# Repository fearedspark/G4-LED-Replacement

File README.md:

# G4 LED Replacement

This project is a high power LED replacement for 12V AC G4 halogen light bulbs.  
The main part of this project is the LED, a CMU1006-000-000N0Z0A30H.

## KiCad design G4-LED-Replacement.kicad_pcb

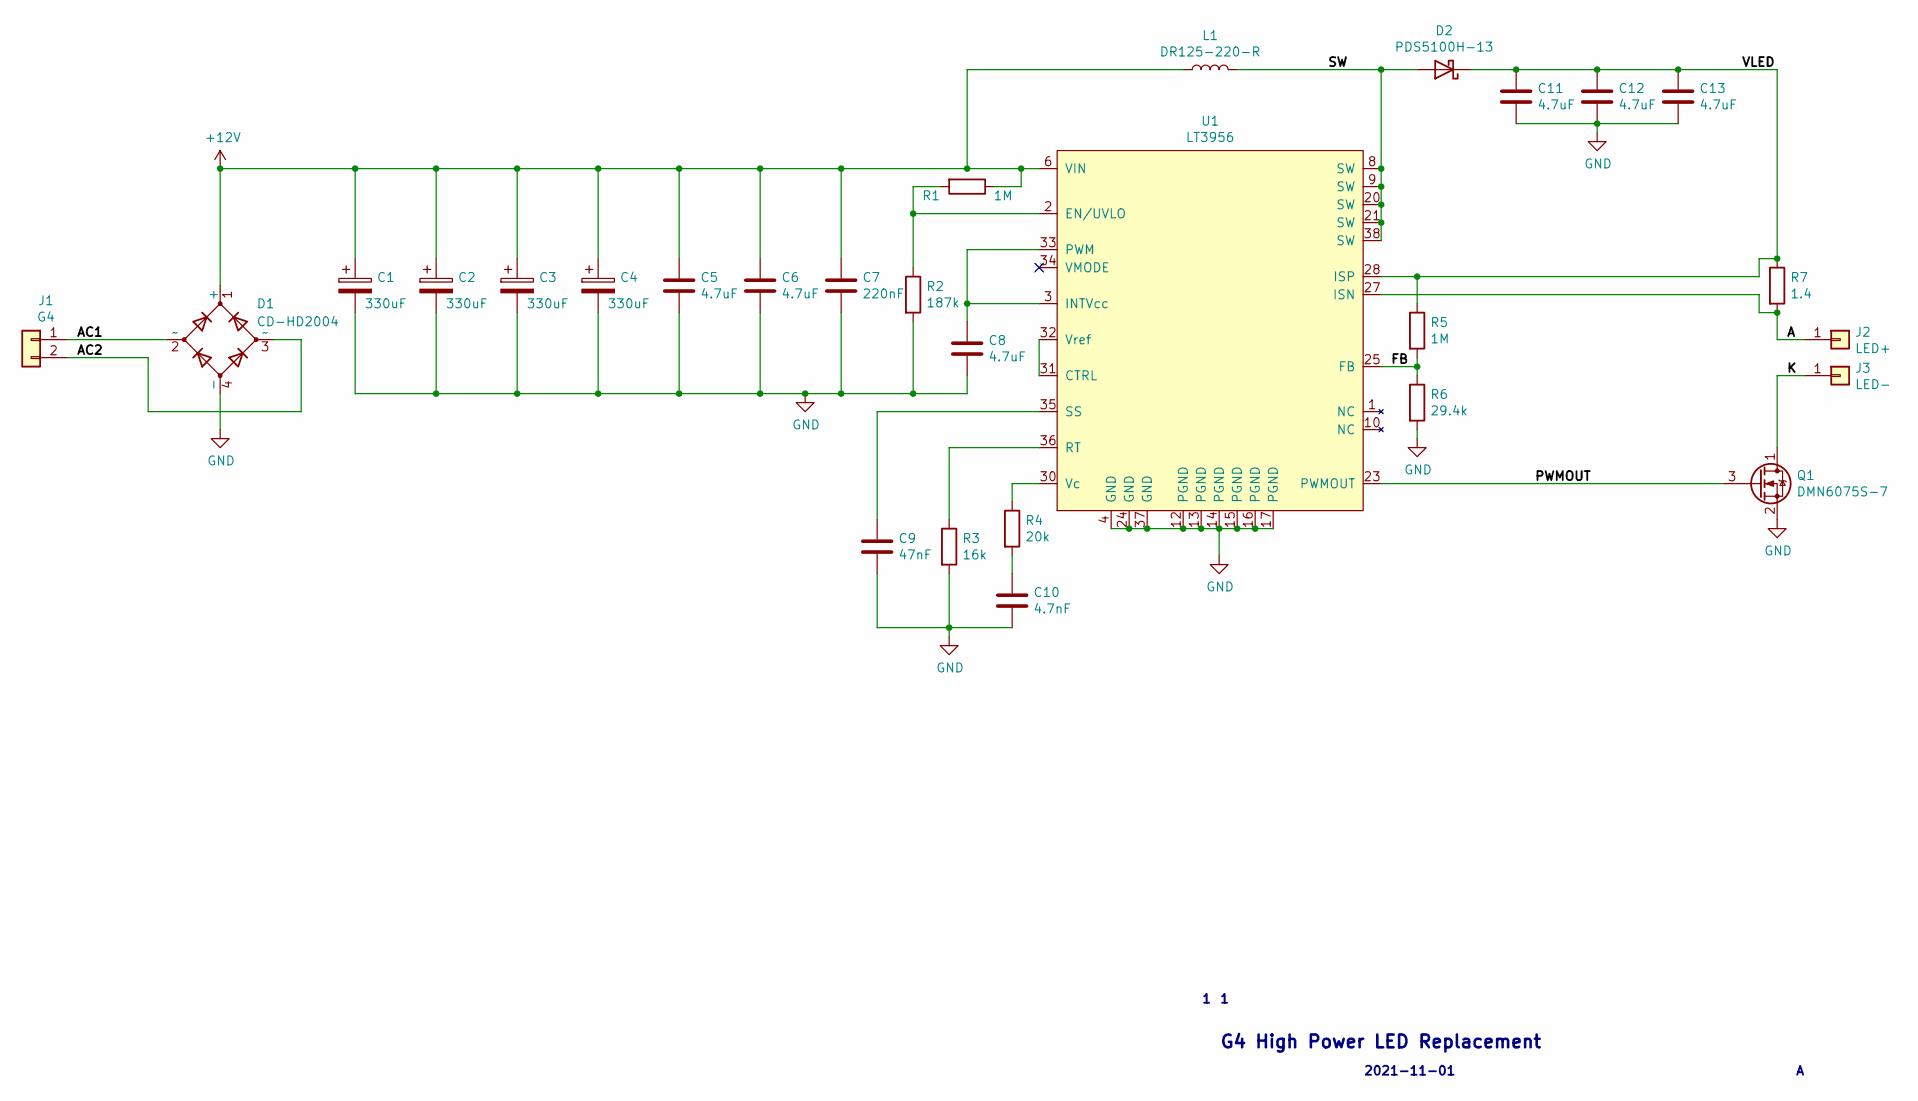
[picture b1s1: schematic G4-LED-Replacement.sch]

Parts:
C1, C2, C3, C4: 330uF; CP_EIA-7361-38_AVX-V
C5, C6, C8: 4.7uF; C_0805_2012Metric
C7: 220nF; C_0402_1005Metric
C9: 47nF; C_0402_1005Metric
C10: 4.7nF; C_0402_1005Metric
C11, C12, C13: 4.7uF; C_1206_3216Metric
D1: CD-HD2004; CD-HD2x(L)
D2: PDS5100H-13; D_PowerDI-5
J1: G4; G4_Pins
J2: LED+; TestPoint_Pad_D4.0mm
J3: LED-; TestPoint_Pad_D4.0mm
L1: DR125-220-R; L_12x12mm_H6mm
Q1: DMN6075S-7; SOT-23
R1, R5: 1M; R_0402_1005Metric
R2: 187k; R_0402_1005Metric
R3: 16k; R_0402_1005Metric
R4: 20k; R_0402_1005Metric
R6: 29.4k; R_0402_1005Metric
R7: 1.4; R_1206_3216Metric
U1: LT3956; 36-UHE

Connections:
+12V: C1.1, C2.1, C3.1, C4.1, C5.1, C6.1, C7.1, D1.1 (+), L1.1, R1.1, U1.6 (VIN)
/A: J2.1, R7.2, U1.27 (ISN)
/AC1: D1.2 (~~), J1.1
/AC2: D1.3 (~~), J1.2
/FB: R5.2, R6.1, U1.25 (FB)
/K: J3.1, Q1.1 (D)
/PWMOUT: Q1.3 (G), U1.23 (PWMOUT)
/SW: D2.2 (A), L1.2, U1.8 (SW), U1.9 (SW), U1.20 (SW), U1.21 (SW), U1.38 (SW)
/VLED: C11.1, C12.1, C13.1, D2.1 (K), R5.1, R7.1, U1.28 (ISP)
GND: C1.2, C2.2, C3.2, C4.2, C5.2, C6.2, C7.2, C8.2, C9.2, C10.2, C11.2, C12.2, C13.2, D1.4 (-), Q1.2 (S), R2.2, R3.2, R6.2, U1.4 (GND), U1.12 (PGND), U1.13 (PGND), U1.14 (PGND), U1.15 (PGND), U1.16 (PGND), U1.17 (PGND), U1.24 (GND), U1.37 (GND)
unnamed: C8.1, U1.3 (INTVcc), U1.33 (PWM)
unnamed: C9.1, U1.35 (SS)
unnamed: C10.1, R4.2
unnamed: R1.2, R2.1, U1.2 (EN/UVLO)
unnamed: R3.1, U1.36 (RT)
unnamed: R4.1, U1.30 (Vc)
unnamed: U1.31 (CTRL), U1.32 (Vref)

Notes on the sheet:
G4 High Power LED Replacement
2021-11-01

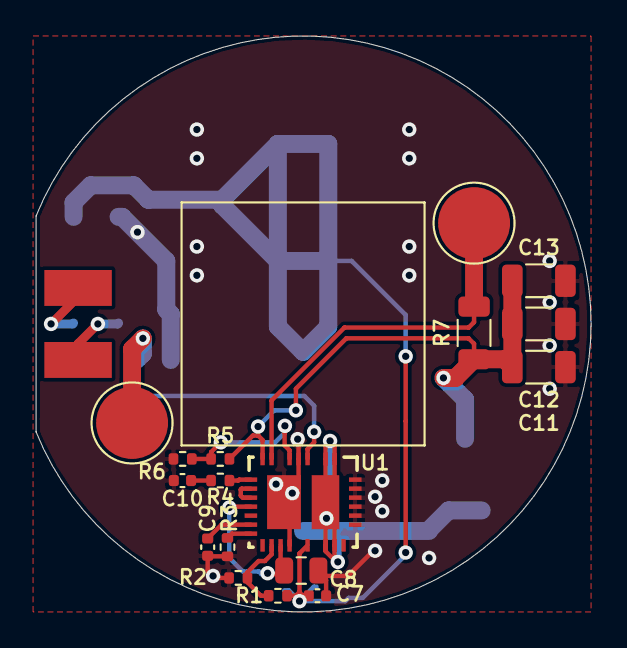
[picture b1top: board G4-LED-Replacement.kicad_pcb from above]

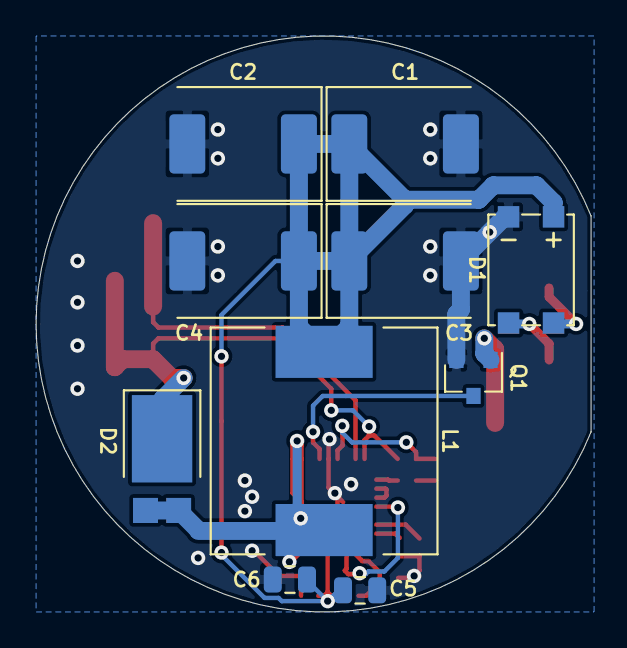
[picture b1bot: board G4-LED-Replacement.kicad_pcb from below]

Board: 2 copper layers, 30.8 x 32.0 mm, 28 parts (10 on the bottom side), 17 nets.

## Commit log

2021-10-31 Created base project files
2021-11-01 Completed initial schematic
2021-11-01 Added routed PCB
